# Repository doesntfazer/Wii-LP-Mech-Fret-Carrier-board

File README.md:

# Wii-LP-Mech-Fret-Carrier-board
A Wii Les Paul Mech fret PCB for the Frets, and the carrier board. These should be drop in replacements for the fret board and carrier board. Carrier board uses an RP2040 zero.

Frets use Choc V1 switches. I recommend using the pro reds or reds if you want to use the bracket.

Cherry MX switches for the strum. You can use whatever switches you want, But I would recommend using Box switches of some kind that are pretty heavy.

[Get the guitar configurator software here](https://github.com/Santroller/Santroller/releases/tag/v10.1.153)

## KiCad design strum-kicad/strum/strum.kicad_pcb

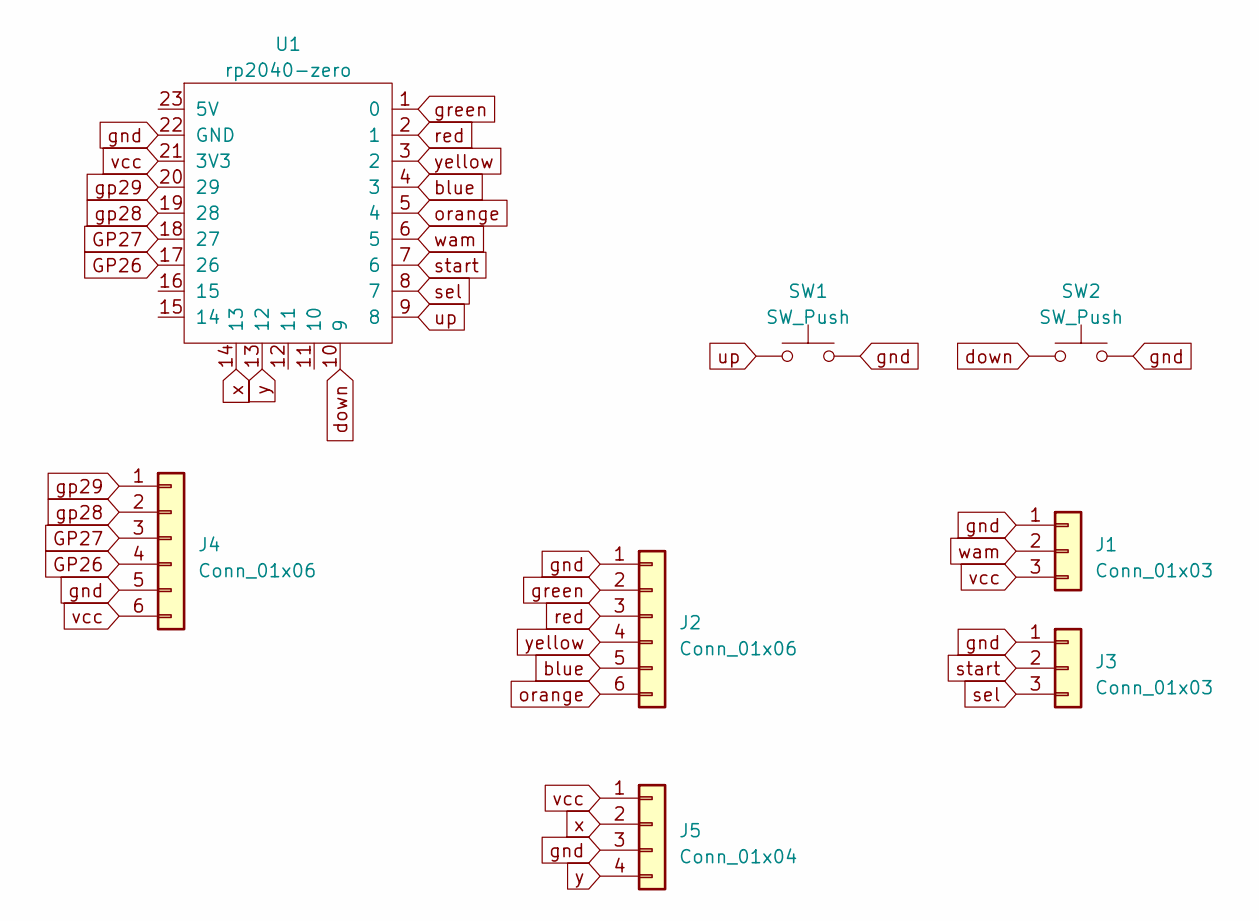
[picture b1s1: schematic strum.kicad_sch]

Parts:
J1, J3: Conn_01x03; PinSocket_1x03_P2.54mm_Vertical
J2, J4: Conn_01x06; PinSocket_1x06_P2.54mm_Vertical
J5: Conn_01x04; PinSocket_1x04_P2.54mm_Vertical
SW1, SW2: SW_Push; SW_Cherry_MX_PCB
U1: rp2040-zero; rp2040-zero-tht

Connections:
GP26: J4.4, U1.17 (26)
GP27: J4.3, U1.18 (27)
blue: J2.5, U1.4 (3)
down: SW2.1, U1.10 (9)
gnd: J1.1, J2.1, J3.1, J4.5, J5.3, SW1.2, SW2.2, U1.22 (GND)
gp28: J4.2, U1.19 (28)
gp29: J4.1, U1.20 (29)
green: J2.2, U1.1 (0)
orange: J2.6, U1.5 (4)
red: J2.3, U1.2 (1)
sel: J3.3, U1.8 (7)
start: J3.2, U1.7 (6)
up: SW1.1, U1.9 (8)
vcc: J1.3, J4.6, J5.1, U1.21 (3V3)
wam: J1.2, U1.6 (5)
x: J5.2, U1.14 (13)
y: J5.4, U1.13 (12)
yellow: J2.4, U1.3 (2)

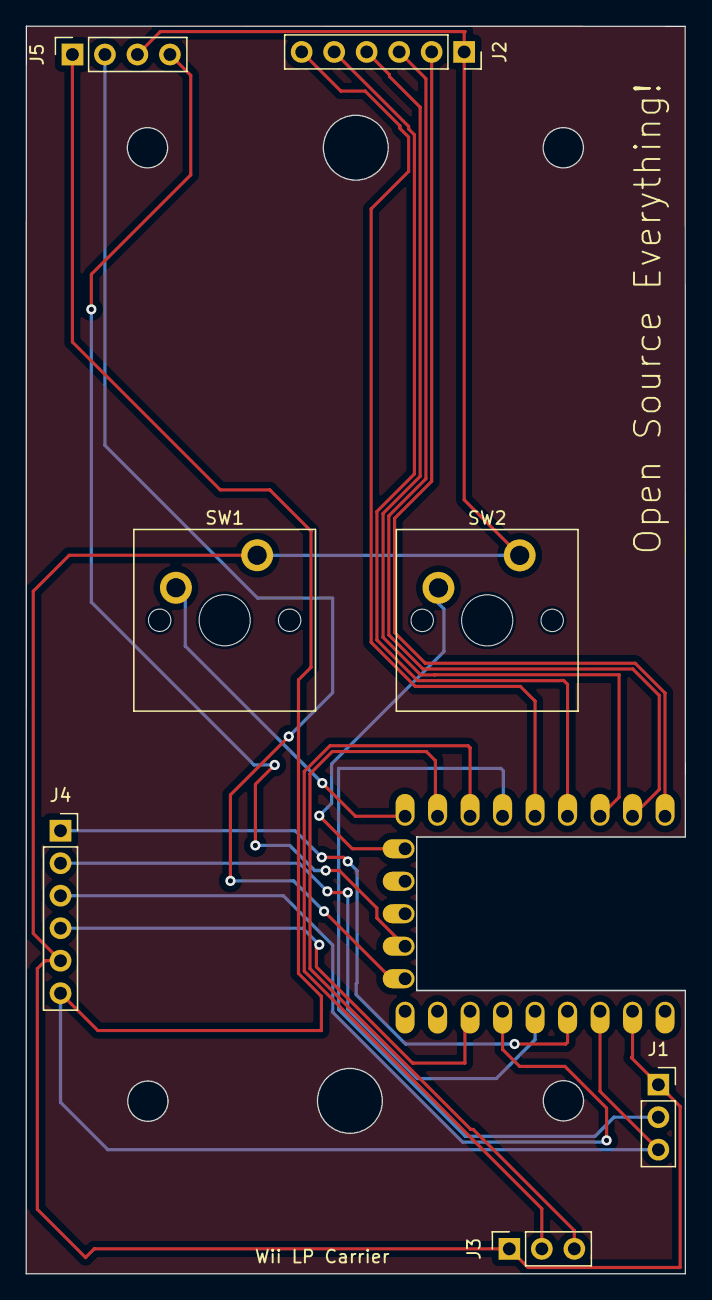
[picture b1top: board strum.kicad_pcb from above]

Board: 2 copper layers, 51.5 x 97.5 mm, 8 parts (1 on the bottom side), 18 nets.

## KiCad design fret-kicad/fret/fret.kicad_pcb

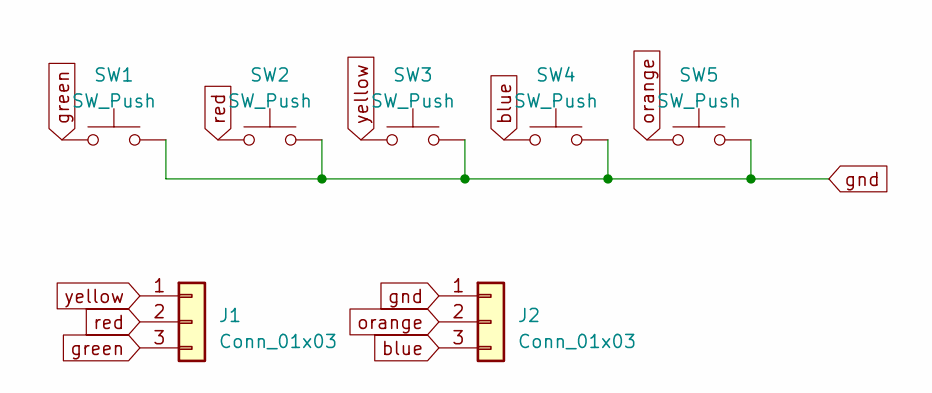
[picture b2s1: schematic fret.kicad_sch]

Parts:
J1, J2: Conn_01x03; PinSocket_1x03_P2.54mm_Vertical
SW1, SW2, SW3, SW4, SW5: SW_Push; Kailh-PG1350-1u-NoLED

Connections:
blue: J2.3, SW4.1
gnd: J2.1, SW1.2, SW2.2, SW3.2, SW4.2, SW5.2
green: J1.3, SW1.1
orange: J2.2, SW5.1
red: J1.2, SW2.1
yellow: J1.1, SW3.1

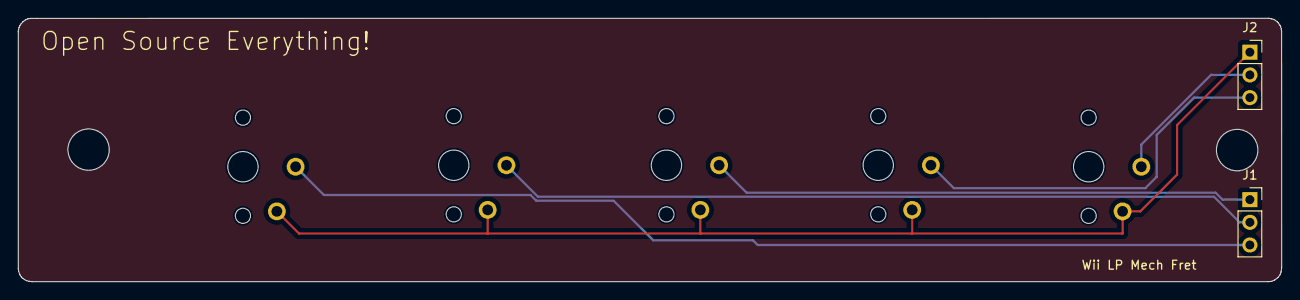
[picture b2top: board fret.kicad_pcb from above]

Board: 2 copper layers, 141.5 x 29.5 mm, 7 parts (0 on the bottom side), 6 nets.

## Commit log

2024-07-26 3d Files - Fret Bracket, Fret buttons
2024-07-26 Dxf files
2024-07-26 Kicad files for fret board
2024-07-26 Carrier board and strum
2024-07-26 Rename bracket.stl to Fret_bracket.stl
